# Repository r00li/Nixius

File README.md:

## Nixius ##
A simple ARM powered Nixie clock.

**Features**

 - It's a clock
 - User settable auto turn on/turn off time (can turn off at night)
 - Manual display on/off button
 - Temperature display

**I want it!**

Great! Build it! This project includes everything that you need. A complete PCB, a 3D printable case and firmware source code.

**Instructions**

 1. Download the project
 2. Manufacture the PCB at your favourite PCB fab (I recommend elecrow.com). I've already included the gerbers so you don't even have to use eagle to export them - they are exported for use with elecrow so you may need to export them again if you want to manufacture them somewhere else.
 3. Order the necessary parts listed in bill of materials (I recommend Farnell/Element 14). Nixies themselves can be bought at siberian-shop.com or somewhere else.
 4. Solder everything together
 5. Flash the firmware to the micro. You will need any STM development board (they can be bought at Farnell for less than 10€) with STLINK. You can compile the project using free EmBlocks IDE (now also called EmBitz). It's a GCC based IDE so it should work with other compilers/IDEs as well. If you don't want to compile the project then you can simply used the .hex file in the bin folder. It's configured for use without the temperature sensor. But compiling everything in EmBlocks should only take a few clicks so I recommend that. 
 6. 3D print the case. It's designed to be 3D printable on most popular home 3D printers. 
 7. Assemble everything and enjoy

I am happy to provide any assistance that you may need. 

**More information**

Hackaday.io: https://hackaday.io/project/5543-nixius

My website: http://www.r00li.com

**Tinkering**

I've used many online sources to build this thing. Especially the power supply part and how to drive the Nixies. Do you want to use some of the bits from my design? Go right ahead! Don't want to use IN-1 nixies? You will just need to replace 4 resistors in the center with the correct ones and you'll be fine. And of course use some wire to connect the nixies. 

**License**

Licensed under GNU GPL v3.

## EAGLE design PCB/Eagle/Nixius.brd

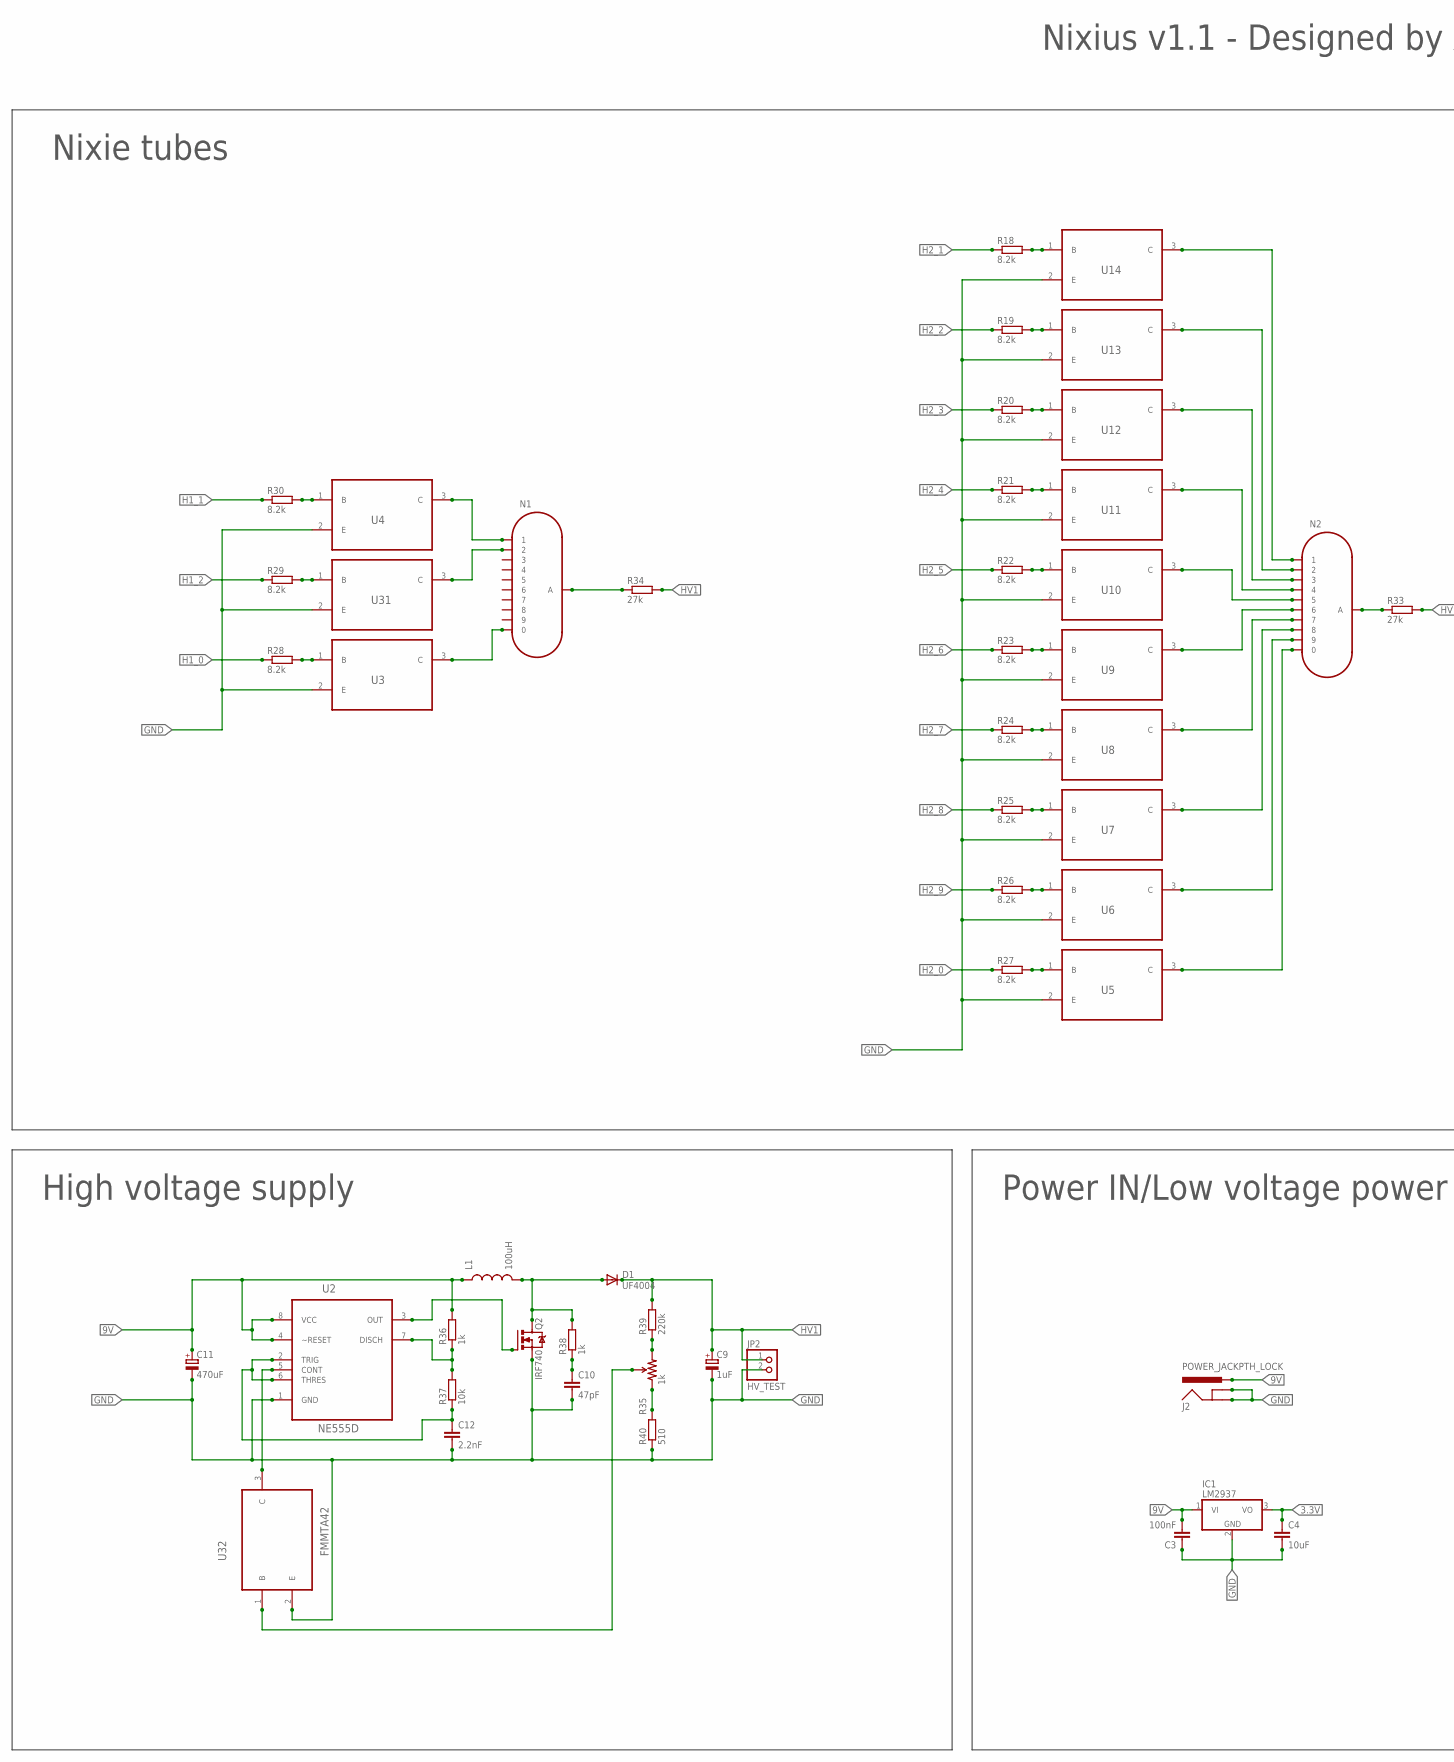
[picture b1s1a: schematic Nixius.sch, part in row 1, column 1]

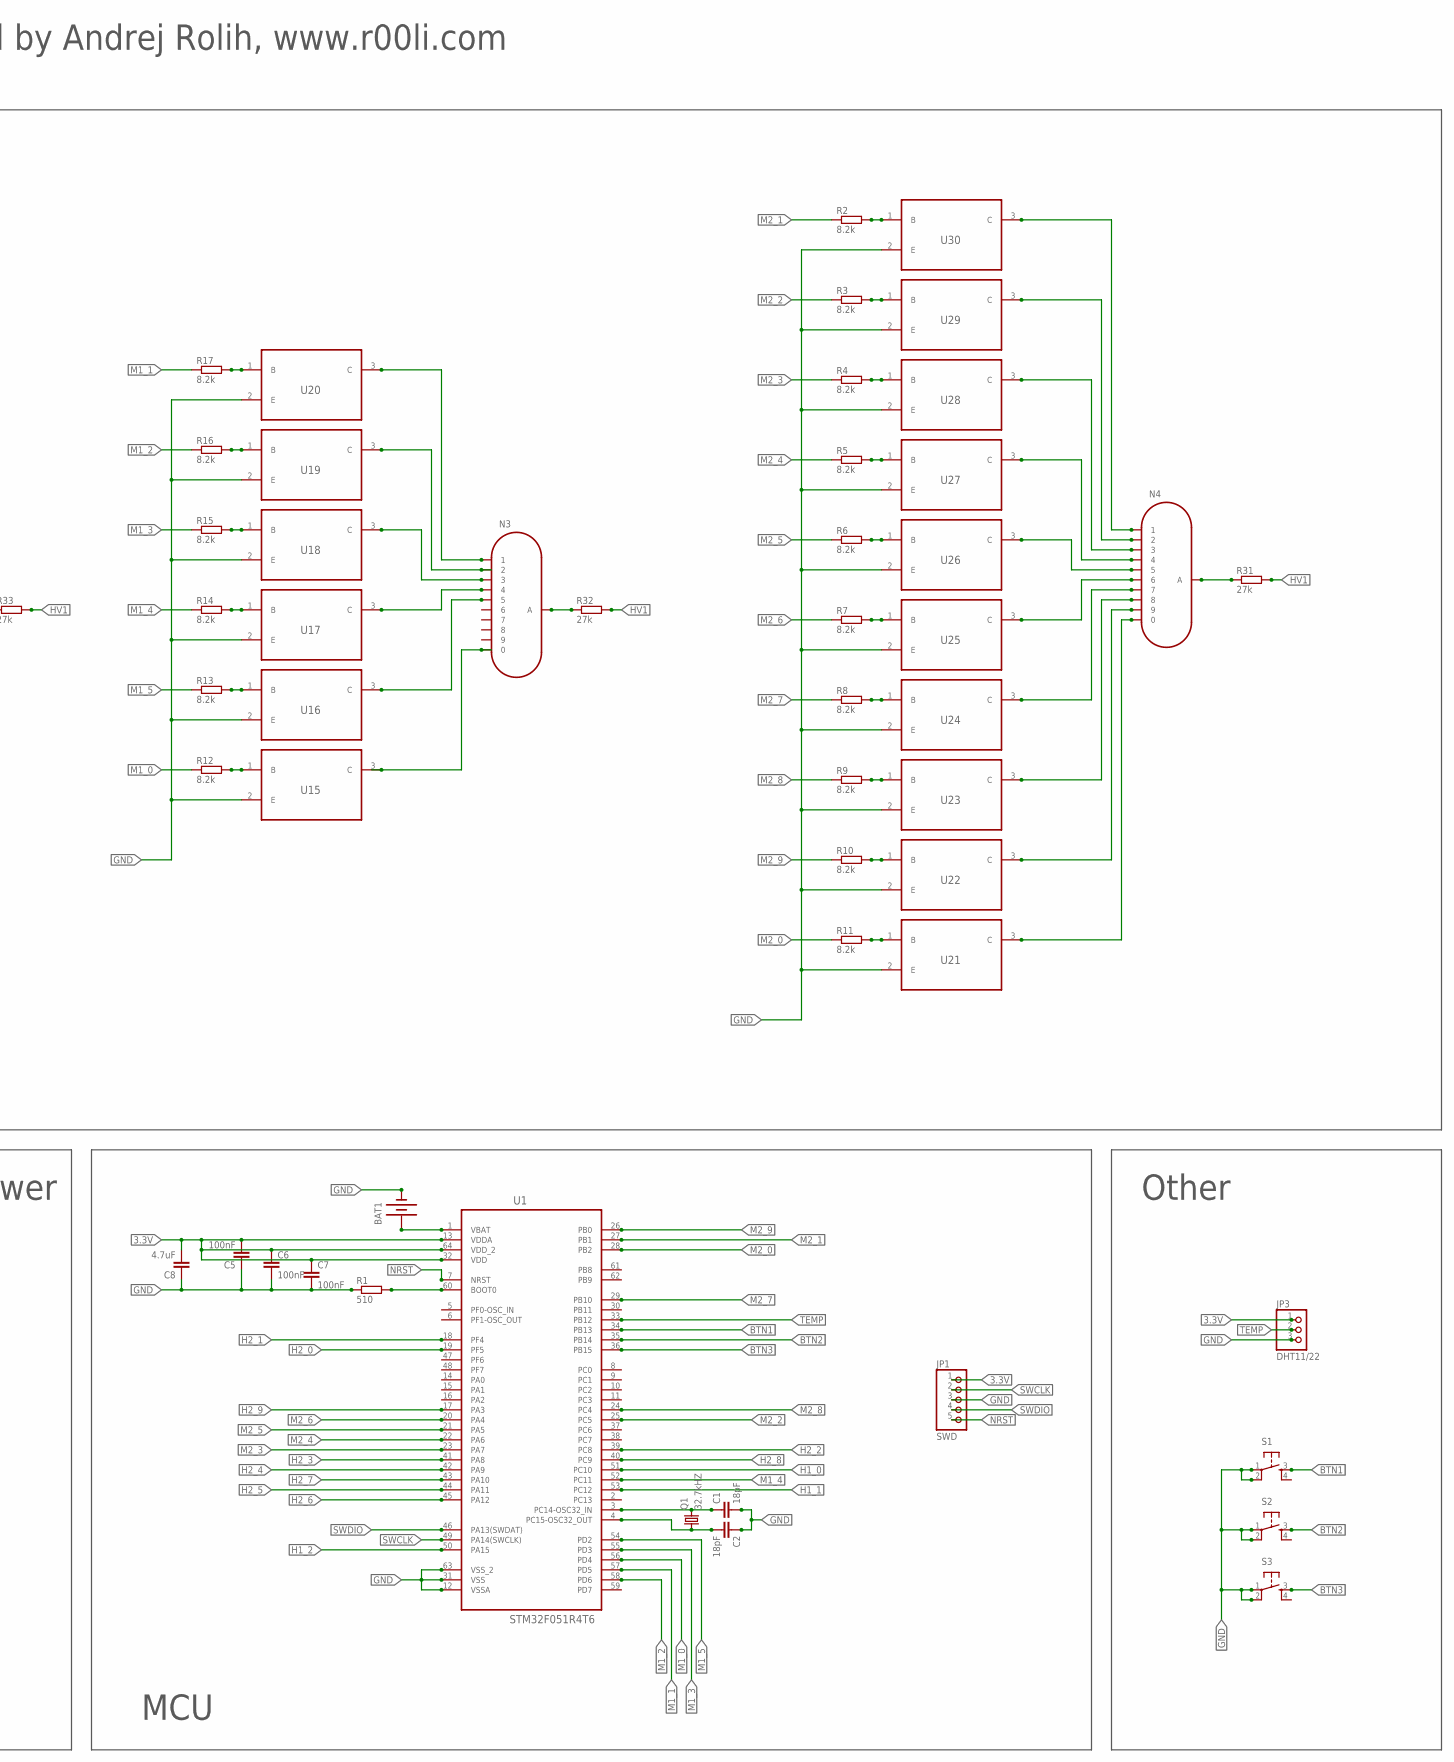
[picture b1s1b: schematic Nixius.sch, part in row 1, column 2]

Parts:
BAT1: BATTERY20SMD; BATTCON_20MM
C1, C2: 18pF; 0805
C3, C5, C6, C7: 100nF; 0805
C4: 10uF; 0805
C8: 4.7uF; 0805
C9: 1uF; E2,5-6
C10: 47pF; 0805
C11: 470uF; E3,5-8
C12: 2.2nF; C050-025X075
D1: UF4004; DO41-10
IC1: LM2937; TO263-3
J2: POWER_JACKPTH_LOCK; POWER_JACK_PTH_LOCK
JP1: SWD; 1X05
JP2: HV_TEST; 1X02
JP3: DHT11/22; 1X03
L1: 100uH; RLB0912
N1, N2, N3, N4: IN-1
Q1: 32.7kHZ; MC-306
Q2: IRF740; TO220BV
R1, R40: 510; R0805
R2, R3, R4, R5, R6, R7, R8, R9, R10, R11, R12, R13, R14, R15, R16, R17, R18, R19, R20, R21, R22, R23, R24, R25, R26, R27, R28, R29, R30: 8.2k; R0805
R31, R32, R33, R34: 27k; R1206
R35: 1k; 3362U-2
R36, R38: 1k; R0805
R37: 10k; R0805
R39: 220k; R1206
S1, S2, S3: TAC_SWITCHPTH; TACTILE-PTH
U1: STM32F051R4T6; QFP50P1200X1200X160-64N
U2: NE555D; SOIC127P600X175-8N
U3, U4, U5, U6, U7, U8, U9, U10, U11, U12, U13, U14, U15, U16, U17, U18, U19, U20, U21, U22, U23, U24, U25, U26, U27, U28, U29, U30, U31, U32: FMMTA42; SOT95P240X110-3N

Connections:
3.3V: C4.1, C5.2, C6.1, C7.1, C8.2, IC1.3 (VO), JP1.1, JP3.1, U1.13 (VDDA), U1.32 (VDD), U1.64 (VDD_2)
9V: C3.2, C11.+, IC1.1 (VI), J2.PWR, L1.1, R36.2, U2.4 (~RESET), U2.8 (VCC)
BTN1: S1.3, U1.34 (PB13)
BTN2: S2.3, U1.35 (PB14)
BTN3: S3.3, U1.36 (PB15)
GND: BAT1.2 (-), C1.2, C2.1, C3.1, C4.2, C5.1, C6.2, C7.2, C8.1, C9.-, C10.2, C11.-, C12.2, IC1.2 (GND), J2.GND, J2.GNDBREAK, JP1.3, JP2.2, JP3.3, Q2.S, R1.1, R40.1, S1.1, S1.2, S2.1, S2.2, S3.1, S3.2, U1.12 (VSSA), U1.31 (VSS), U1.63 (VSS_2), U2.1 (GND), U3.2 (E), U4.2 (E), U5.2 (E), U6.2 (E), U7.2 (E), U8.2 (E), U9.2 (E), U10.2 (E), U11.2 (E), U12.2 (E), U13.2 (E), U14.2 (E), U15.2 (E), U16.2 (E), U17.2 (E), U18.2 (E), U19.2 (E), U20.2 (E), U21.2 (E), U22.2 (E), U23.2 (E), U24.2 (E), U25.2 (E), U26.2 (E), U27.2 (E), U28.2 (E), U29.2 (E), U30.2 (E), U31.2 (E), U32.2 (E)
H1_0: R28.1, U1.51 (PC10)
H1_1: R30.1, U1.53 (PC12)
H1_2: R29.1, U1.50 (PA15)
H2_0: R27.1, U1.19 (PF5)
H2_1: R18.1, U1.18 (PF4)
H2_2: R19.1, U1.39 (PC8)
H2_3: R20.1, U1.41 (PA8)
H2_4: R21.1, U1.42 (PA9)
H2_5: R22.1, U1.44 (PA11)
H2_6: R23.1, U1.45 (PA12)
H2_7: R24.1, U1.43 (PA10)
H2_8: R25.1, U1.40 (PC9)
H2_9: R26.1, U1.17 (PA3)
HV1: C9.+, D1.C, JP2.1, R31.2, R32.2, R33.2, R34.2, R39.2
M1_0: R12.1, U1.56 (PD4)
M1_1: R17.1, U1.57 (PD5)
M1_2: R16.1, U1.58 (PD6)
M1_3: R15.1, U1.55 (PD3)
M1_4: R14.1, U1.52 (PC11)
M1_5: R13.1, U1.54 (PD2)
M2_0: R11.1, U1.28 (PB2)
M2_1: R2.1, U1.27 (PB1)
M2_2: R3.1, U1.25 (PC5)
M2_3: R4.1, U1.23 (PA7)
M2_4: R5.1, U1.22 (PA6)
M2_5: R6.1, U1.21 (PA5)
M2_6: R7.1, U1.20 (PA4)
M2_7: R8.1, U1.29 (PB10)
M2_8: R9.1, U1.24 (PC4)
M2_9: R10.1, U1.26 (PB0)
unnamed: N1.0, U3.3 (C)
unnamed: N1.2, U31.3 (C)
unnamed: N1.1, U4.3 (C)
unnamed: N2.0, U5.3 (C)
unnamed: N2.9, U6.3 (C)
unnamed: N2.8, U7.3 (C)
unnamed: N2.7, U8.3 (C)
unnamed: N2.6, U9.3 (C)
unnamed: N2.5, U10.3 (C)
unnamed: N2.4, U11.3 (C)
unnamed: N2.3, U12.3 (C)
unnamed: N2.2, U13.3 (C)
unnamed: N2.1, U14.3 (C)
unnamed: N3.0, U15.3 (C)
unnamed: N3.5, U16.3 (C)
unnamed: N3.4, U17.3 (C)
unnamed: N3.3, U18.3 (C)
unnamed: N3.2, U19.3 (C)
unnamed: N3.1, U20.3 (C)
unnamed: N4.0, U21.3 (C)
unnamed: N4.9, U22.3 (C)
unnamed: N4.8, U23.3 (C)
unnamed: N4.7, U24.3 (C)
unnamed: N4.6, U25.3 (C)
unnamed: N4.5, U26.3 (C)
unnamed: N4.4, U27.3 (C)
unnamed: N4.3, U28.3 (C)
unnamed: N4.2, U29.3 (C)
unnamed: N4.1, U30.3 (C)
unnamed: BAT1.1 (+), U1.1 (VBAT)
unnamed: C1.1, Q1.4 (2), U1.3 (PC14-OSC32_IN)
unnamed: C2.2, Q1.1, U1.4 (PC15-OSC32_OUT)
unnamed: R1.2, U1.60 (BOOT0)
unnamed: R30.2, U4.1 (B)
unnamed: R29.2, U31.1 (B)
unnamed: R28.2, U3.1 (B)
unnamed: R18.2, U14.1 (B)
unnamed: R19.2, U13.1 (B)
unnamed: R20.2, U12.1 (B)
unnamed: R21.2, U11.1 (B)
unnamed: R22.2, U10.1 (B)
unnamed: R23.2, U9.1 (B)
unnamed: R24.2, U8.1 (B)
unnamed: R25.2, U7.1 (B)
unnamed: R26.2, U6.1 (B)
unnamed: R27.2, U5.1 (B)
unnamed: R17.2, U20.1 (B)
unnamed: R16.2, U19.1 (B)
unnamed: R15.2, U18.1 (B)
unnamed: R14.2, U17.1 (B)
unnamed: R13.2, U16.1 (B)
unnamed: R12.2, U15.1 (B)
unnamed: R2.2, U30.1 (B)
unnamed: R3.2, U29.1 (B)
unnamed: R4.2, U28.1 (B)
unnamed: R5.2, U27.1 (B)
unnamed: R6.2, U26.1 (B)
unnamed: R7.2, U25.1 (B)
unnamed: R8.2, U24.1 (B)
unnamed: R9.2, U23.1 (B)
unnamed: R10.2, U22.1 (B)
unnamed: R11.2, U21.1 (B)
unnamed: N1.A, R34.1
unnamed: N3.A, R32.1
unnamed: R36.1, R37.2, U2.7 (DISCH)
unnamed: U2.5 (CONT), U32.3 (C)
unnamed: C12.1, R37.1, U2.2 (TRIG), U2.6 (THRES)
unnamed: Q2.G, U2.3 (OUT)
unnamed: D1.A, L1.2, Q2.D, R38.2
unnamed: C10.1, R38.1
unnamed: R35.3 (CW), R39.1
unnamed: R35.1 (CCW), R40.2
unnamed: N2.A, R33.1
unnamed: R35.2 (WIPER), U32.1 (B)
unnamed: N4.A, R31.1
NRST: JP1.5, U1.7 (NRST)
SWCLK: JP1.2, U1.49 (PA14(SWCLK))
SWDIO: JP1.4, U1.46 (PA13(SWDAT))
TEMP: JP3.2, U1.33 (PB12)

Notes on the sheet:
Nixie tubes
High voltage supply
Power IN/Low voltage power
MCU
Other
Nixius v1.1 - Designed by Andrej Rolih, www.r00li.com

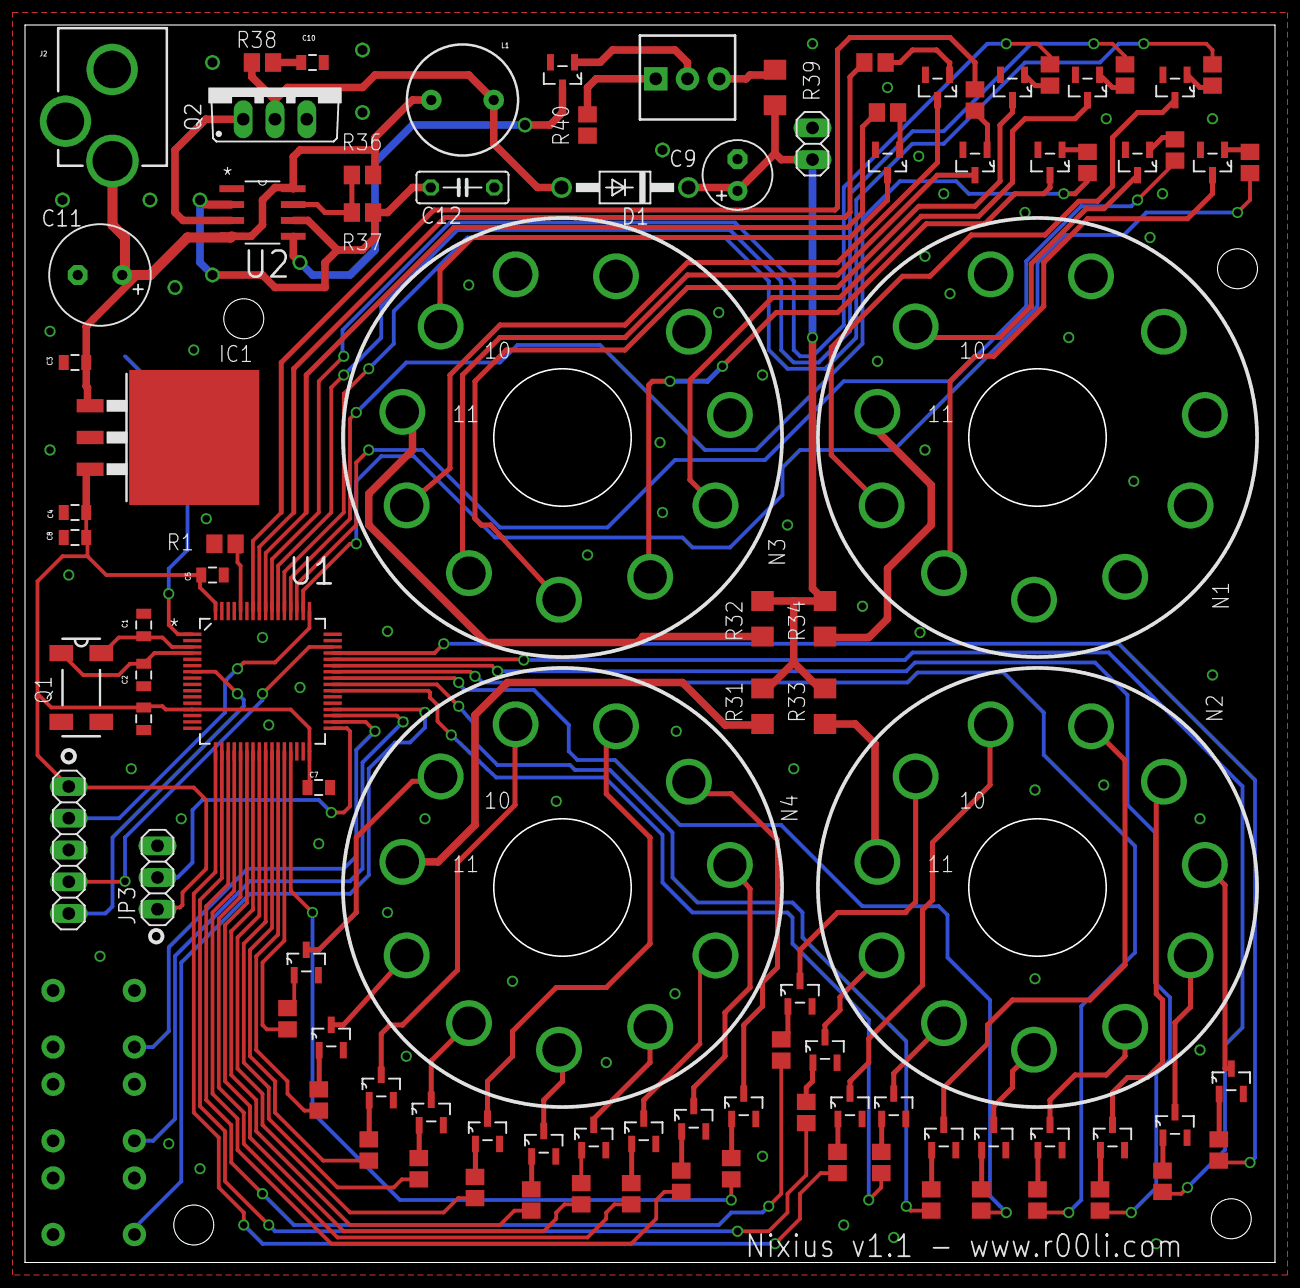
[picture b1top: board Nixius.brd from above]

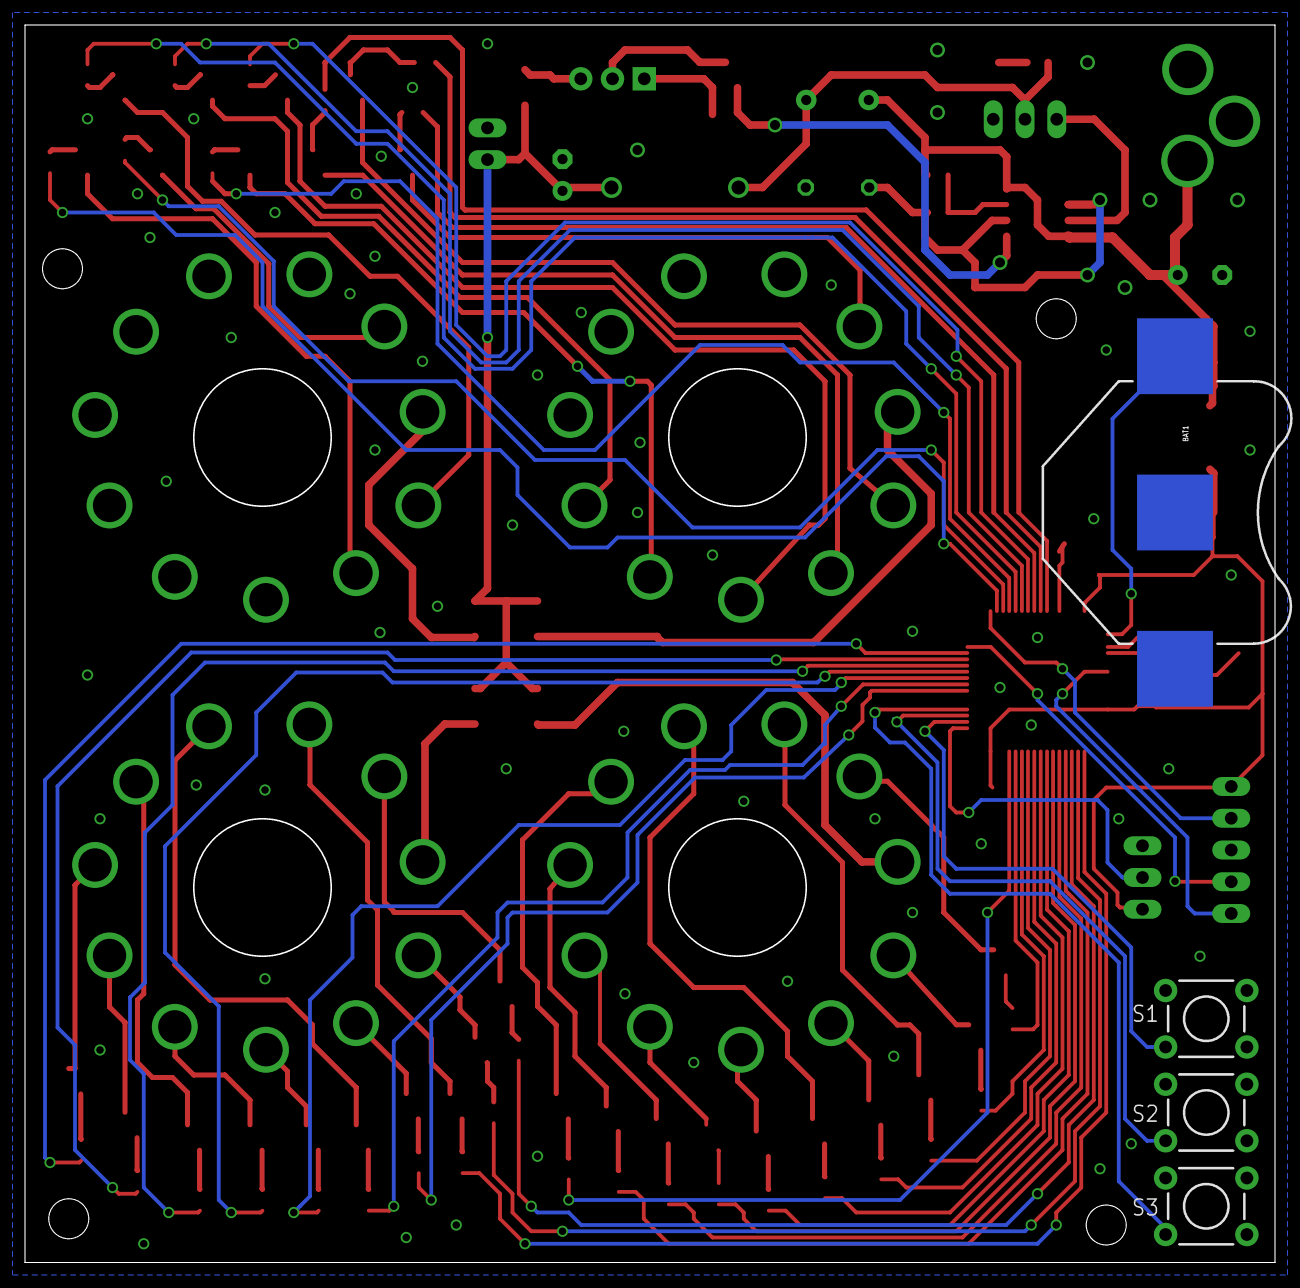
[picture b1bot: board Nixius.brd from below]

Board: 2 copper layers, 99.9 x 98.9 mm, 101 parts (4 on the bottom side), 115 nets.

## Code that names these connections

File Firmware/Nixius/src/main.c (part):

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#include "essentials.h"
#include "dht22.h"

#define Pin_H1_0 GPIOC,GPIO_Pin_10
#define Pin_H1_1 GPIOC,GPIO_Pin_12
#define Pin_H1_2 GPIOA,GPIO_Pin_15

#define Pin_H2_0 GPIOF,GPIO_Pin_5
#define Pin_H2_1 GPIOF,GPIO_Pin_4
#define Pin_H2_2 GPIOC,GPIO_Pin_8
#define Pin_H2_3 GPIOA,GPIO_Pin_8
#define Pin_H2_4 GPIOA,GPIO_Pin_9
#define Pin_H2_5 GPIOA,GPIO_Pin_11
#define Pin_H2_6 GPIOA,GPIO_Pin_12
#define Pin_H2_7 GPIOA,GPIO_Pin_10
#define Pin_H2_8 GPIOC,GPIO_Pin_9
#define Pin_H2_9 GPIOA,GPIO_Pin_3

#define Pin_M1_0 GPIOB,GPIO_Pin_4
#define Pin_M1_1 GPIOB,GPIO_Pin_5
#define Pin_M1_2 GPIOB,GPIO_Pin_6
#define Pin_M1_3 GPIOB,GPIO_Pin_3
#define Pin_M1_4 GPIOC,GPIO_Pin_11
#define Pin_M1_5 GPIOD,GPIO_Pin_2

#define Pin_M2_0 GPIOB,GPIO_Pin_2
#define Pin_M2_1 GPIOB,GPIO_Pin_1
#define Pin_M2_2 GPIOC,GPIO_Pin_5
#define Pin_M2_3 GPIOA,GPIO_Pin_7
#define Pin_M2_4 GPIOA,GPIO_Pin_6
#define Pin_M2_5 GPIOA,GPIO_Pin_5
#define Pin_M2_6 GPIOA,GPIO_Pin_4
#define Pin_M2_7 GPIOB,GPIO_Pin_10
#define Pin_M2_8 GPIOC,GPIO_Pin_4
#define Pin_M2_9 GPIOB,GPIO_Pin_0

#define Tube_H1 0
#define Tube_H2 1
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{
    if (tube == Tube_H1)
    {
        GPIO_ResetBits(Pin_H1_0);
        GPIO_ResetBits(Pin_H1_1);
        GPIO_ResetBits(Pin_H1_2);
    }
    else if (tube == Tube_H2)
    {
        GPIO_ResetBits(Pin_H2_0);
        GPIO_ResetBits(Pin_H2_1);
        GPIO_ResetBits(Pin_H2_2);
        GPIO_ResetBits(Pin_H2_3);
        GPIO_ResetBits(Pin_H2_4);
        GPIO_ResetBits(Pin_H2_5);
        GPIO_ResetBits(Pin_H2_6);
        GPIO_ResetBits(Pin_H2_7);
        GPIO_ResetBits(Pin_H2_8);
        GPIO_ResetBits(Pin_H2_9);
    }
    else if (tube == Tube_M1)
    {
        GPIO_ResetBits(Pin_M1_0);
        GPIO_ResetBits(Pin_M1_1);
        GPIO_ResetBits(Pin_M1_2);
        GPIO_ResetBits(Pin_M1_3);
        GPIO_ResetBits(Pin_M1_4);
        GPIO_ResetBits(Pin_M1_5);
    }
    else if (tube == Tube_M2)
    {
        GPIO_ResetBits(Pin_M2_0);
        GPIO_ResetBits(Pin_M2_1);
        GPIO_ResetBits(Pin_M2_2);
        GPIO_ResetBits(Pin_M2_3);
        GPIO_ResetBits(Pin_M2_4);
        GPIO_ResetBits(Pin_M2_5);
        GPIO_ResetBits(Pin_M2_6);
        GPIO_ResetBits(Pin_M2_7);
        GPIO_ResetBits(Pin_M2_8);
        GPIO_ResetBits(Pin_M2_9);
    }
}

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    {
        switch (number)
        {
            case 0: GPIO_SetBits(Pin_H1_0); break;
            case 1: GPIO_SetBits(Pin_H1_1); break;
            case 2: GPIO_SetBits(Pin_H1_2); break;
        }
    }
    else if (tube == Tube_H2)
    {
        switch (number)
        {
            case 0: GPIO_SetBits(Pin_H2_0); break;
            case 1: GPIO_SetBits(Pin_H2_1); break;
            case 2: GPIO_SetBits(Pin_H2_2); break;
            case 3: GPIO_SetBits(Pin_H2_3); break;
            case 4: GPIO_SetBits(Pin_H2_4); break;
            case 5: GPIO_SetBits(Pin_H2_5); break;
            case 6: GPIO_SetBits(Pin_H2_6); break;
            case 7: GPIO_SetBits(Pin_H2_7); break;
            case 8: GPIO_SetBits(Pin_H2_8); break;
            case 9: GPIO_SetBits(Pin_H2_9); break;
        }
    }
    else if (tube == Tube_M1)
    {
        switch (number)
        {
            case 0: GPIO_SetBits(Pin_M1_0); break;
            case 1: GPIO_SetBits(Pin_M1_1); break;
            case 2: GPIO_SetBits(Pin_M1_2); break;
            case 3: GPIO_SetBits(Pin_M1_3); break;
            case 4: GPIO_SetBits(Pin_M1_4); break;
            case 5: GPIO_SetBits(Pin_M1_5); break;
        }
    }
    else if (tube == Tube_M2)
    {
        switch (number)
        {
            case 0: GPIO_SetBits(Pin_M2_0); break;
            case 1: GPIO_SetBits(Pin_M2_1); break;
            case 2: GPIO_SetBits(Pin_M2_2); break;
            case 3: GPIO_SetBits(Pin_M2_3); break;
            case 4: GPIO_SetBits(Pin_M2_4); break;
            case 5: GPIO_SetBits(Pin_M2_5); break;
            case 6: GPIO_SetBits(Pin_M2_6); break;
            case 7: GPIO_SetBits(Pin_M2_7); break;
            case 8: GPIO_SetBits(Pin_M2_8); break;
            case 9: GPIO_SetBits(Pin_M2_9); break;
        }
    }
}
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
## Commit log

2015-07-19 Version 1 commit
2015-07-19 Fixed Readme file
2015-07-19 Fixed readme 2

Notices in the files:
Firmware/Nixius/src/main.c:
For licensing see included License file
parts and their libraries:
SparkFun-Connectors: Licensing: CC v3.0 Share-Alike You are welcome to use this library for commercial purposes.
